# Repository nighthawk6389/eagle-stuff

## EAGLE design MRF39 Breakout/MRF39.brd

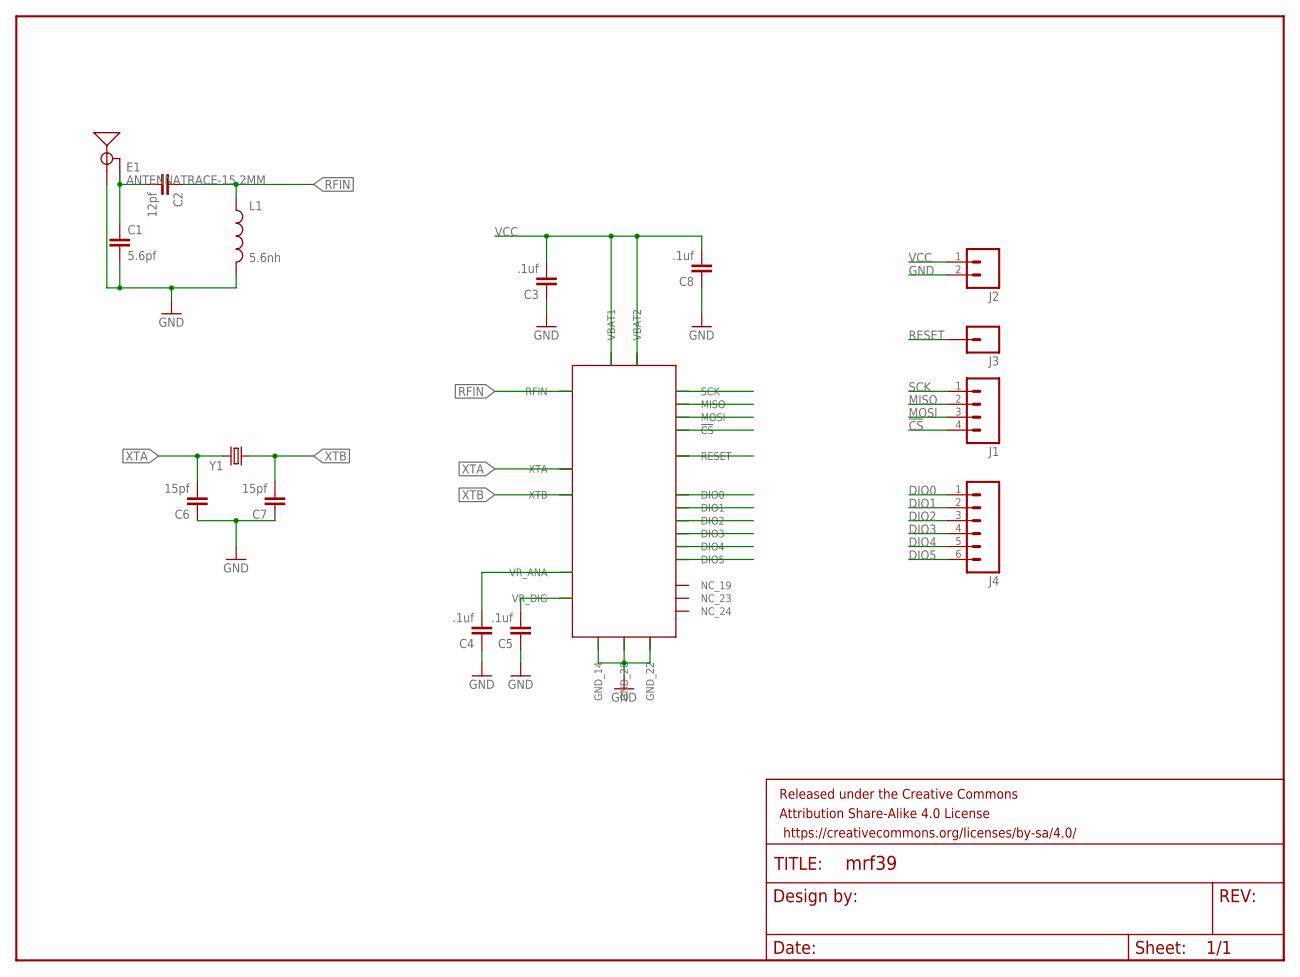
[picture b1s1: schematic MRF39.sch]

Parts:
C1: 5.6pf; 0603-CAP
C2: 12pf; 0603-CAP
C3, C4, C5, C8: .1uf; 0603-CAP
C6, C7: 15pf; 0603-CAP
E1: ANTENNATRACE-15.2MM; TRACE_ANTENNA_2.4GHZ_15.2MM
FRAME1: FRAME-LETTERNO_PACKAGE; DUMMY
J1: M04PTH; 1X04
J2: M02PTH; 1X02
J3: M01PTH; 1X01
J4: M06SILK_FEMALE_PTH; 1X06
L1: 5.6nh; 0805
U1: MRF39RATQFN24; QFN24-5X5X1.0
Y1: CRYSTALSMD; HC49UP

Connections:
!CS: J1.4, U1.18 (!CS)
DIO0: J4.1, U1.7 (DIO0)
DIO1: J4.2, U1.8 (DIO1)
DIO2: J4.3, U1.9 (DIO2)
DIO3: J4.4, U1.10 (DIO3)
DIO4: J4.5, U1.11 (DIO4)
DIO5: J4.6, U1.12 (DIO5)
GND: C1.2, C3.1, C4.1, C5.1, C6.1, C7.1, C8.1, E1.ANT (SIGNAL), J2.2, L1.2, U1.14 (GND_14), U1.20 (GND_20), U1.22 (GND_22)
MISO: J1.2, U1.16 (MISO)
MOSI: J1.3, U1.17 (MOSI)
unnamed: C5.2, U1.3 (VR_DIG)
unnamed: C4.2, U1.2 (VR_ANA)
unnamed: C1.1, C2.2, E1.GND
RESET: J3.1, U1.6 (RESET)
RFIN: C2.1, L1.1, U1.21 (RFIN)
SCK: J1.1, U1.15 (SCK)
VCC: C3.2, C8.2, J2.1, U1.1 (VBAT1), U1.13 (VBAT2)
XTA: C6.2, U1.4 (XTA), Y1.2
XTB: C7.2, U1.5 (XTB), Y1.1

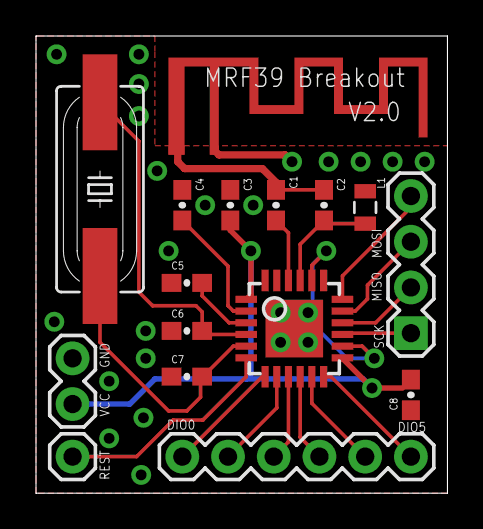
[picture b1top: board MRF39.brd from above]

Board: 2 copper layers, 22.9 x 25.4 mm, 18 parts (1 on the bottom side), 19 nets.

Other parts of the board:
U$1: OSHW-LOGO-L

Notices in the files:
parts and their libraries:
SparkFun-Capacitors: Licensing: Creative Commons ShareAlike 4.0 International - https://creativecommons.org/licenses/by-sa/4.0
SparkFun-Aesthetics: Released under the Creative Commons Attribution Share-Alike 4.0 License
SparkFun-Aesthetics: https://creativecommons.org/licenses/by-sa/4.0
